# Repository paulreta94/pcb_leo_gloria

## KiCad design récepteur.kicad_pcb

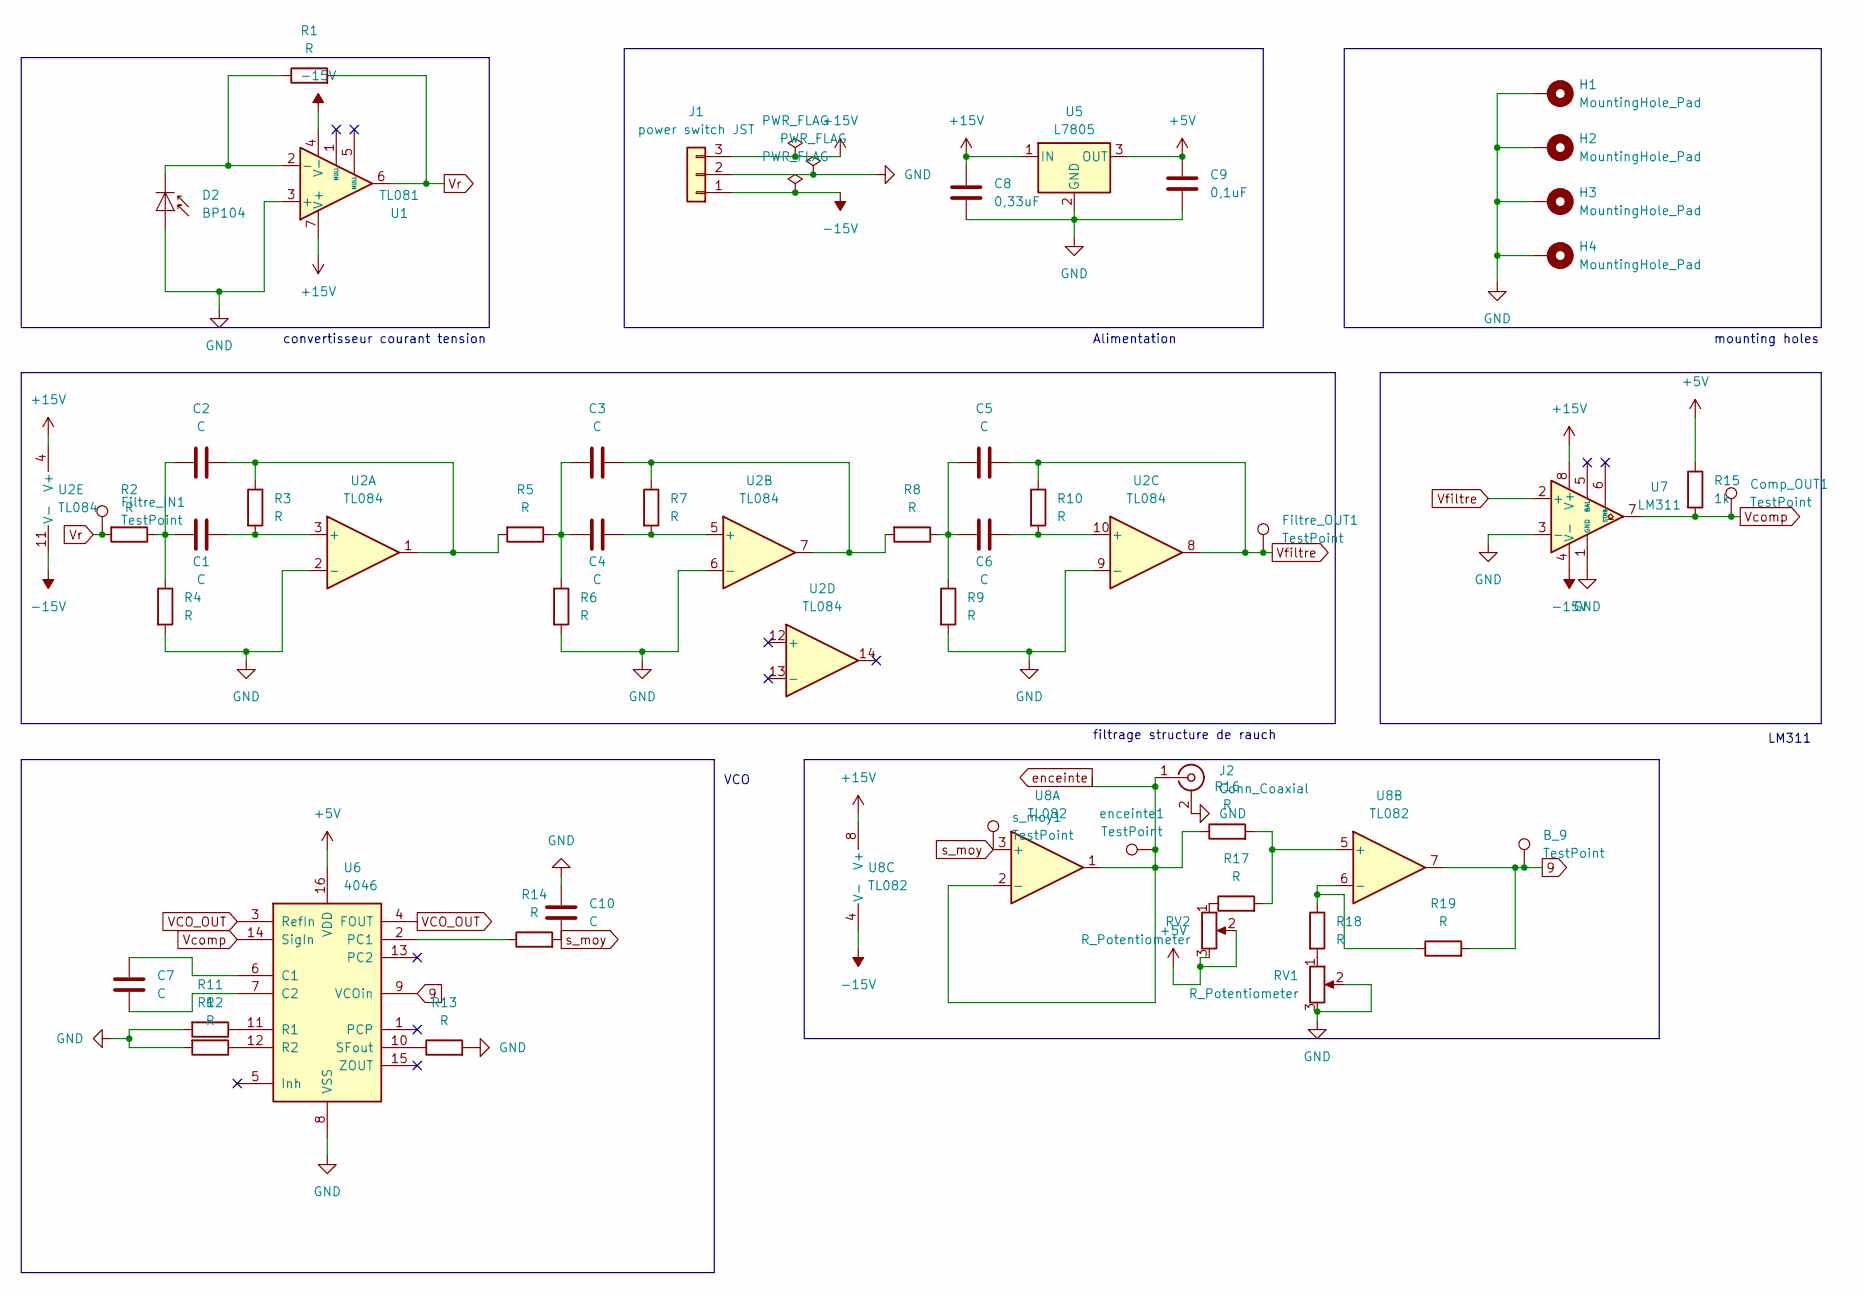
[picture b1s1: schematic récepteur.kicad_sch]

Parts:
B_9: TestPoint; TestPoint_Plated_Hole_D2.0mm
C1, C2, C3, C4, C5, C6, C7, C10: C; C_0603_1608Metric_Pad1.08x0.95mm_HandSolder
C8: 0,33uF; C_0603_1608Metric_Pad1.08x0.95mm_HandSolder
C9: 0,1uF; C_0603_1608Metric_Pad1.08x0.95mm_HandSolder
Comp_OUT1: TestPoint; TestPoint_Plated_Hole_D2.0mm
D2: BP104; Osram_DIL2_4.3x4.65mm_P5.08mm
Filtre_IN1: TestPoint; TestPoint_Plated_Hole_D2.0mm
Filtre_OUT1: TestPoint; TestPoint_Plated_Hole_D2.0mm
H1, H2, H3, H4: MountingHole_Pad; MountingHole_3.2mm_M3_DIN965_Pad
J1: power switch JST; JST_XH_S3B-XH-A_1x03_P2.50mm_Horizontal
J2: Conn_Coaxial; BNC_Amphenol_031-5539_Vertical
R1, R2, R3, R4, R5, R6, R7, R8, R9, R10, R11, R12, R13, R14, R16, R17, R18, R19: R; R_0603_1608Metric_Pad0.98x0.95mm_HandSolder
R15: 1k; R_0603_1608Metric_Pad0.98x0.95mm_HandSolder
RV1, RV2: R_Potentiometer; Potentiometer_Vishay_TS53YJ_Vertical
U1: TL081; SOIC-8-1EP_3.9x4.9mm_P1.27mm_EP2.29x3mm
U2: TL084; SOIC-14_3.9x8.7mm_P1.27mm
U5: L7805; TO-220-3_Vertical
U6: 4046; DIP-16_W7.62mm_LongPads
U7: LM311; SOIC-8-1EP_3.9x4.9mm_P1.27mm_EP2.29x3mm
U8: TL082; SOIC-8-1EP_3.9x4.9mm_P1.27mm_EP2.29x3mm
enceinte1: TestPoint; TestPoint_Plated_Hole_D2.0mm
s_moy1: TestPoint; TestPoint_Plated_Hole_D2.0mm

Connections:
9: B_9.1, R19.2, U6.9 (VCOin), U8.7
+5V: C9.1, R15.1, RV2.2, RV2.3, U5.3 (OUT), U6.16 (VDD)
+15V: C8.1, J1.3, U1.7 (V+), U2.4 (V+), U5.1 (IN), U7.8 (V+), U8.8 (V+)
-15V: J1.1, U1.4 (V-), U2.11 (V-), U7.4 (V-), U8.4 (V-)
GND: C8.2, C9.2, C10.1, D2.2 (A), H1.1, H2.1, H3.1, H4.1, J1.2, J2.2 (Ext), R4.2, R6.2, R9.2, R11.2, R12.2, R13.2, RV1.2, RV1.3, U1.3 (+), U2.2 (-), U2.6 (-), U2.9 (-), U5.2 (GND), U6.8 (VSS), U7.1 (GND), U7.3 (-)
unnamed: C1.1, C2.1, R2.1, R4.1
unnamed: C2.2, R3.1, R5.2, U2.1
unnamed: C3.1, C4.1, R5.1, R6.1
unnamed: C3.2, R7.1, R8.2, U2.7
unnamed: C5.1, C6.1, R8.1, R9.1
unnamed: D2.1 (K), R1.1, U1.2 (-)
unnamed: R17.1, RV2.1
unnamed: R18.2, RV1.1
unnamed: C1.2, R3.2, U2.3 (+)
unnamed: C4.2, R7.2, U2.5 (+)
unnamed: C6.2, R10.2, U2.10 (+)
unnamed: C7.1, U6.6 (C1)
unnamed: C7.2, U6.7 (C2)
unnamed: R14.1, U6.2 (PC1)
unnamed: R11.1, U6.11 (R1)
unnamed: R12.1, U6.12 (R2)
unnamed: R13.1, U6.10 (SFout)
unnamed: R16.2, R17.2, U8.5 (+)
unnamed: R18.1, R19.1, U8.6 (-)
VCO_OUT: U6.3 (RefIn), U6.4 (FOUT)
Vcomp: Comp_OUT1.1, R15.2, U6.14 (SigIn), U7.7
Vfiltre: C5.2, Filtre_OUT1.1, R10.1, U2.8, U7.2 (+)
Vr: Filtre_IN1.1, R1.2, R2.2, U1.6
enceinte: J2.1 (In), R16.1, U8.1, U8.2 (-), enceinte1.1
s_moy: C10.2, R14.2, U8.3 (+), s_moy1.1

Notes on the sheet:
Alimentation
convertisseur courant tension
VCO
filtrage structure de rauch
mounting holes
LM311

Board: 4 copper layers, 50 parts (0 on the bottom side), 30 nets, no tracks yet.

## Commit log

2024-03-13 Version du 13 mars 2024 16:49
